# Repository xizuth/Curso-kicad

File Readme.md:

# Curso básico de KiCad

Curso básico de Kicad desde el proceso de instalación hasta culminar con una PCB.
Se desarrolla una PCB utilizando un NE555, construyendo un osculador Astable, desde la face de creación del esquemático hasta su terminanción en una PCB.

## Curso en YouTube

[Lista de reproducción en YouTube](https://www.youtube.com/playlist?list=PLE7RuMYW0W5Di71-aiWNUxpenKBAk5KDZ)

- [1. Instalación y prueba de kiCad en windows](https://youtu.be/QeJxQIdk3iI)
- [2. Creando esquemático en kicad](https://youtu.be/BZhZgBaz_h0)
- [3. Agregando más detalles a esquemático kicad](https://youtu.be/TywXVqaktTU)
- [4. Cómo exportar diagrama esquemático kicad](https://youtu.be/NpxuoHJrbj8)
- [5. Introducción a qué son los footprint](https://youtu.be/b3a9KcL0cfA)
- [6. Asignando footprint a componentes kicad](https://youtu.be/LjzxLj3viCg)
- [7. Aprendiendo más sobre footprints y package de componentes electrónicos kicad](https://youtu.be/rXnbt5xWTdQ)
- [8. Creando PCB desde cero del esquemático kicad](https://youtu.be/4rYowXPnbXY)
- [9. Personalizando PCB kicad](https://youtu.be/jkqt4m4lfhA)
- [10. Exportando pcb para impresión kicad](https://youtu.be/TpHnDHIXOLU)

## Archivos

### Esquemático

### 3D

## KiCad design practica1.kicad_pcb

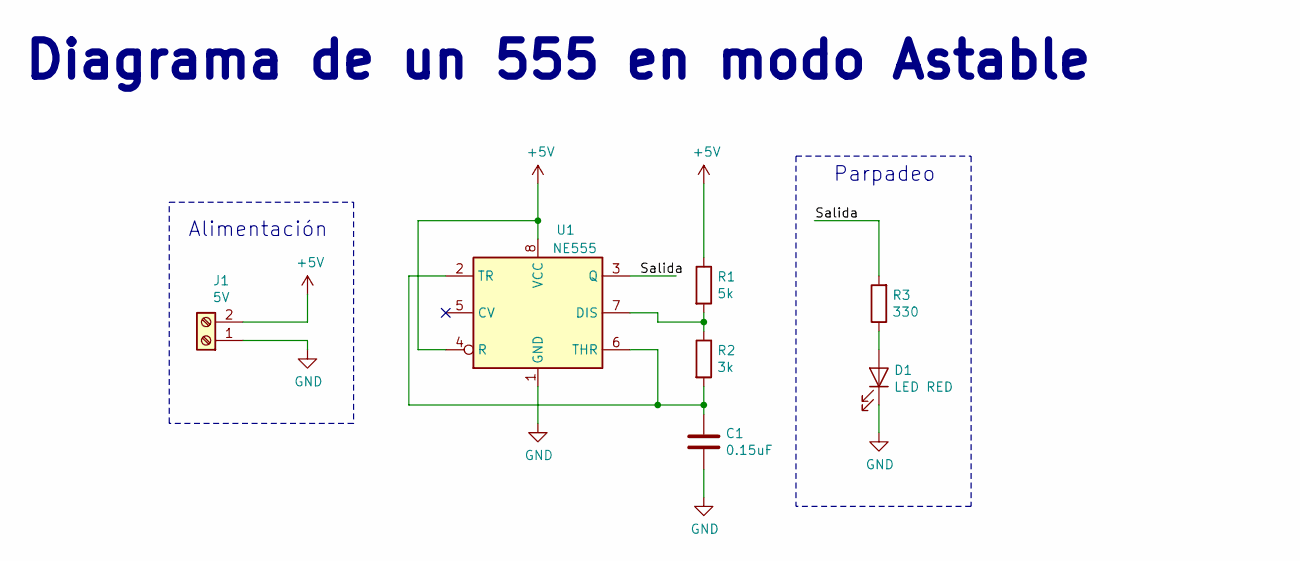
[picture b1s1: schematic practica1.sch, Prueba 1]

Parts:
C1: 0.15uF; C_Disc_D4.3mm_W1.9mm_P5.00mm
D1: LED RED; LED_D5.0mm
J1: 5V; PinHeader_1x02_P2.54mm_Vertical
R1: 5k; R_Axial_DIN0309_L9.0mm_D3.2mm_P12.70mm_Horizontal
R2: 3k; R_Axial_DIN0309_L9.0mm_D3.2mm_P12.70mm_Horizontal
R3: 330; R_Axial_DIN0309_L9.0mm_D3.2mm_P12.70mm_Horizontal
U1: NE555; DIP-8_W7.62mm_LongPads

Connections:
+5V: J1.2, R1.1, U1.4 (R), U1.8 (VCC)
/Salida: R3.2, U1.3 (Q)
GND: C1.2, D1.1 (K), J1.1, U1.1 (GND)
unnamed: C1.1, R2.2, U1.2 (TR), U1.6 (THR)
unnamed: D1.2 (A), R3.1
unnamed: R1.2, R2.1, U1.7 (DIS)

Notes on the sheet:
Diagrama de un 555 en modo Astable
Parpadeo
Alimentación

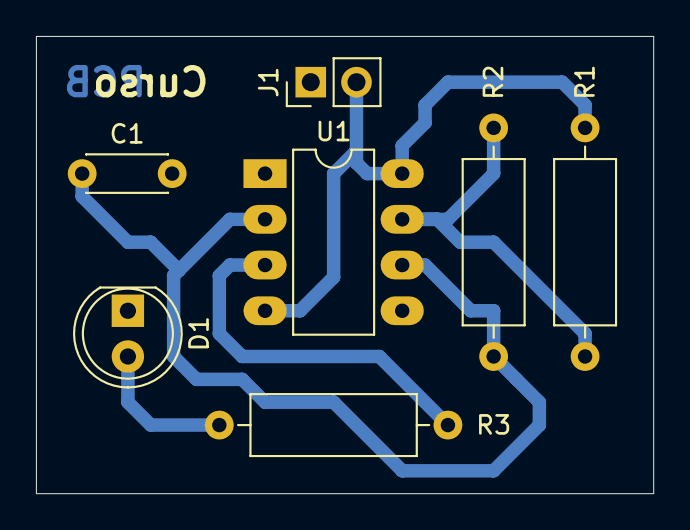
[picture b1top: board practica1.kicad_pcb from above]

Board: 2 copper layers, 34.3 x 25.4 mm, 7 parts (0 on the bottom side), 6 nets.

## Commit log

2019-04-22 init commit
2019-04-22 readme
2019-04-25 datasheet
2019-04-27 3D for freecad
